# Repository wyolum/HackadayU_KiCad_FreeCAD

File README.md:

# HackadayU_KiCad_FreeCAD
Repo for KiCad and FreeCAD project for HackadayU classes

Hackaday.io Project https://hackaday.io/project/172360-introduction-to-kicad-and-freecad

## KiCad

* [KiCad](/KiCad) - EDA hardware design files - Schematic, Layout etc.

## FreeCAD

* [FreeCAD](/FreeCAD) - 3D CAD hardware design files - Enclosure

## images

* [images](/images) - Renders, screenshots etc.

## datasheets

* [datasheets](/datasheets) - Component datasheets, drawings

## youtube
 * course 1: https://www.youtube.com/watch?v=ignWMyRbPYM
 * course 2: https://www.youtube.com/watch?v=JeOZMAFZbqI
 * course 3: https://www.youtube.com/watch?v=cOB0TuuFBug
 * course 4: https://www.youtube.com/watch?v=lbnrUtgFFCc

License
-------
[CERN Open Hardware Licence v1.2 ]

[CERN Open Hardware Licence v1.2 ]:http://www.ohwr.org/attachments/2388/cern_ohl_v_1_2.txt

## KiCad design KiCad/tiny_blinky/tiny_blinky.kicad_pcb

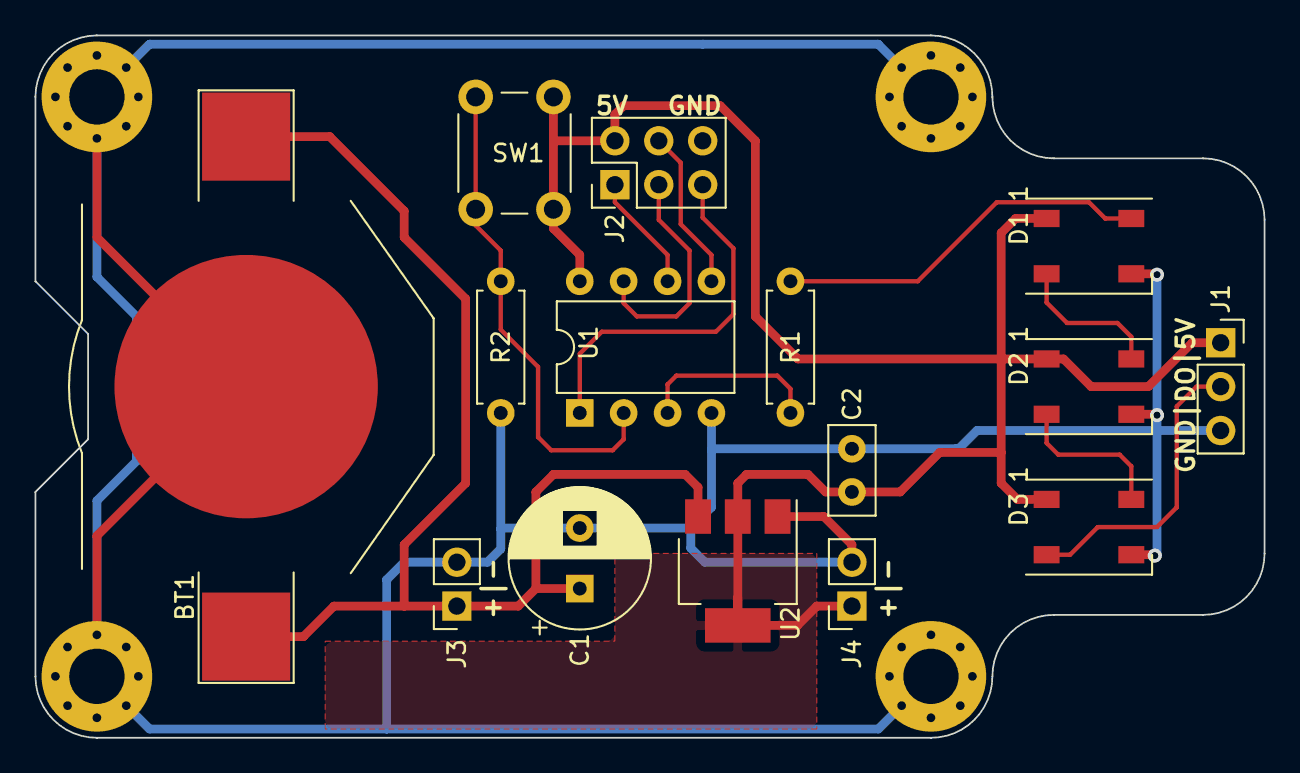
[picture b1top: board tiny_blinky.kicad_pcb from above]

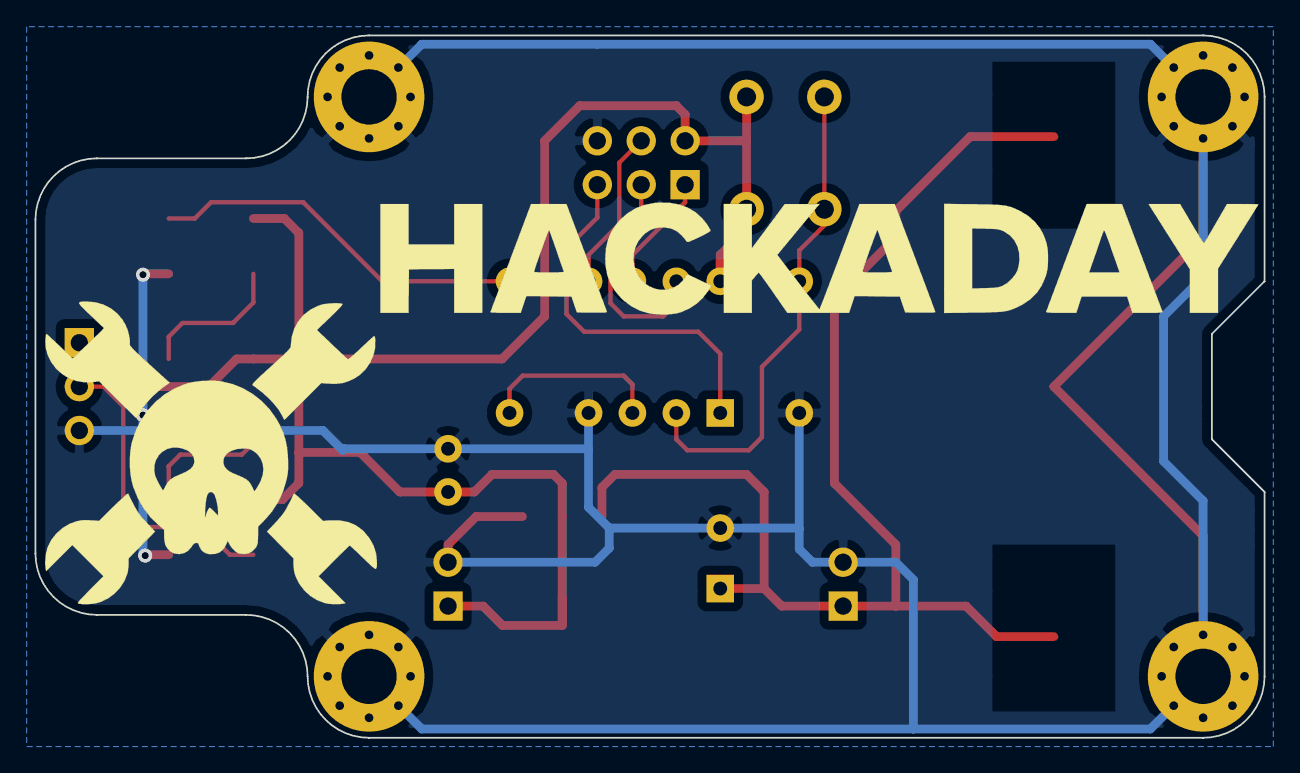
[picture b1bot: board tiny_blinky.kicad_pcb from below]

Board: 2 copper layers, 71.1 x 40.6 mm, 21 parts (2 on the bottom side), 13 nets.

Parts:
BT1: 2xCR2032; BatteryHolder_Keystone_3024-2x2032
C1: 470uF/25V; CP_Radial_D8.0mm_P3.50mm
C2: 100n; C_Disc_D5.0mm_W2.5mm_P2.50mm
D1, D2, D3: WS2812B; LED_WS2812B_PLCC4_5.0x5.0mm_P3.2mm
G1: LOGO_skull; logo_skull
G2: LOGO_hackaday; logo_hackaday
H1, H2, H3, H4: MountingHole_Pad; MountingHole_3.2mm_M3_Pad_Via
J1: Dout; PinSocket_1x03_P2.54mm_Vertical
J2: SPI; PinHeader_2x03_P2.54mm_Vertical
J3: Vin; PinSocket_1x02_P2.54mm_Vertical
J4: 5V; PinSocket_1x02_P2.54mm_Vertical
R1: 330E; R_Axial_DIN0207_L6.3mm_D2.5mm_P7.62mm_Horizontal
R2: 10k; R_Axial_DIN0207_L6.3mm_D2.5mm_P7.62mm_Horizontal
SW1: SW; SW_PUSH_6mm_H5mm
U1: ATtiny85-20PU; DIP-8_W7.62mm
U2: AP1117-50; SOT-223-3_TabPin2

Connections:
/5V: C2.1, D1.1, D2.1, D3.1, J1.1, J2.2, J4.1, SW1.1, U1.8, U2.2
/D1: D1.2, D2.4
/D2: D2.2, D3.4
/Din: D1.4, R1.1
/Dout: D3.2, J1.2
/PB0: J2.4, U1.5
/PB1: J2.1, U1.6
/PB2: J2.3, U1.7
/PB5: J2.5, U1.1
/Tiny_Blinky_Power/Vin: BT1.1, C1.1, J3.1, U2.3
GND: BT1.2, C1.2, C2.2, D1.3, D2.3, D3.3, H1.1, H2.1, H3.1, H4.1, J1.3, J2.6, J3.2, J4.2, R2.2, U1.4, U2.1
unnamed: R1.2, U1.3
unnamed: R2.1, SW1.2, U1.2

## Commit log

2020-07-13 Session 2 updates
2020-07-30 Session 3 & 4 updates
2020-07-30 added reference enclosure design
2021-01-22 added links to the youtube courses
